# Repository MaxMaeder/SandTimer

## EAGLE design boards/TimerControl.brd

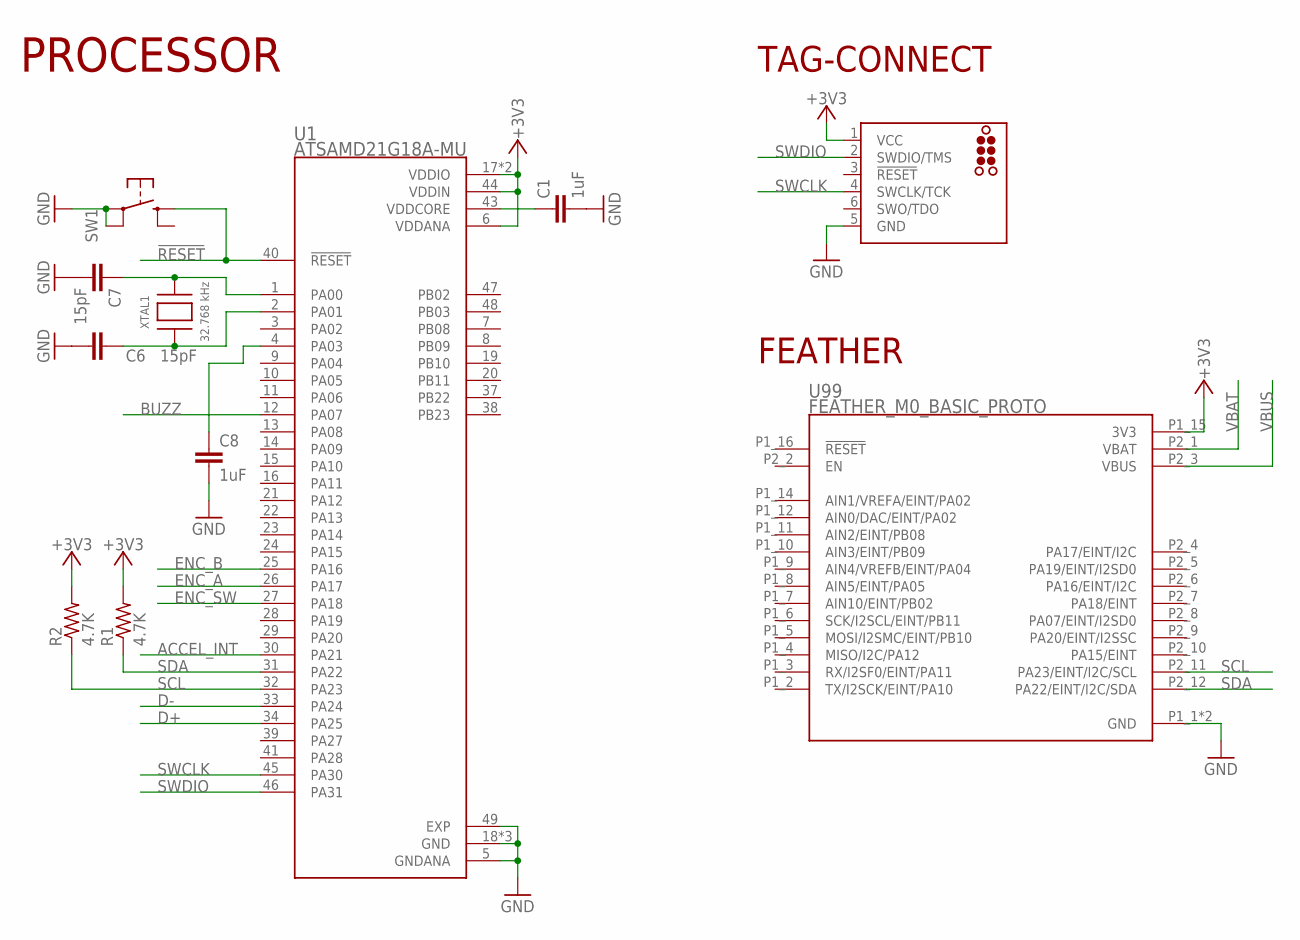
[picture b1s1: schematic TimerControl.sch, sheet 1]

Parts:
C1, C8: 1uF; C0603
C6, C7: 15pF; C0603
J3: TC2030_SWD-MCP-NL; TC2030-MCP-NL
R1, R2: 4.7K; R0603
SW1: KMR2; 2.80X4.60
U1: ATSAMD21G18A-MU; QFN50P700X700X90-49N
U99: FEATHER_M0_BASIC_PROTO; MODULE_FEATHER_M0_BASIC_PROTO
XTAL1: 32.768 kHz; XTAL3215

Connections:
!RESET: SW1.B (S), U1.40 (!RESET)
+3V3: J3.1 (VCC), R1.2, R2.2, U1.6 (VDDANA), U1.17 (VDDIO), U1.36 (VDDIO), U1.44 (VDDIN), U99.P1_15 (3V3); also elsewhere on the board
ACCEL_INT: U1.30 (PA21); also elsewhere on the board
BUZZ: U1.12 (PA07); also elsewhere on the board
D+: U1.34 (PA25); also elsewhere on the board
D-: U1.33 (PA24); also elsewhere on the board
ENC_A: U1.26 (PA17); also elsewhere on the board
ENC_B: U1.25 (PA16); also elsewhere on the board
ENC_SW: U1.27 (PA18); also elsewhere on the board
GND: C1.2, C6.2, C7.2, C8.2, J3.5 (GND), SW1.A, SW1.A' (P1), U1.5 (GNDANA), U1.18 (GND), U1.35 (GND), U1.42 (GND), U1.49 (EXP), U99.P1_1 (GND), U99.P1_13 (GND); also elsewhere on the board
unnamed: C1.1, U1.43 (VDDCORE)
unnamed: C8.1, U1.4 (PA03)
unnamed: C6.1, U1.2 (PA01), XTAL1.P$1
unnamed: C7.1, U1.1 (PA00), XTAL1.P$2
SCL: R2.1, U1.32 (PA23), U99.P2_11 (PA23/EINT/I2C/SCL); also elsewhere on the board
SDA: R1.1, U1.31 (PA22), U99.P2_12 (PA22/EINT/I2C/SDA); also elsewhere on the board
SWCLK: J3.4 (SWCLK/TCK), U1.45 (PA30)
SWDIO: J3.2 (SWDIO/TMS), U1.46 (PA31)
VBAT: U99.P2_1 (VBAT); also elsewhere on the board
VBUS: U99.P2_3 (VBUS); also elsewhere on the board

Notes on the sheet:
TAG-CONNECT
PROCESSOR
FEATHER

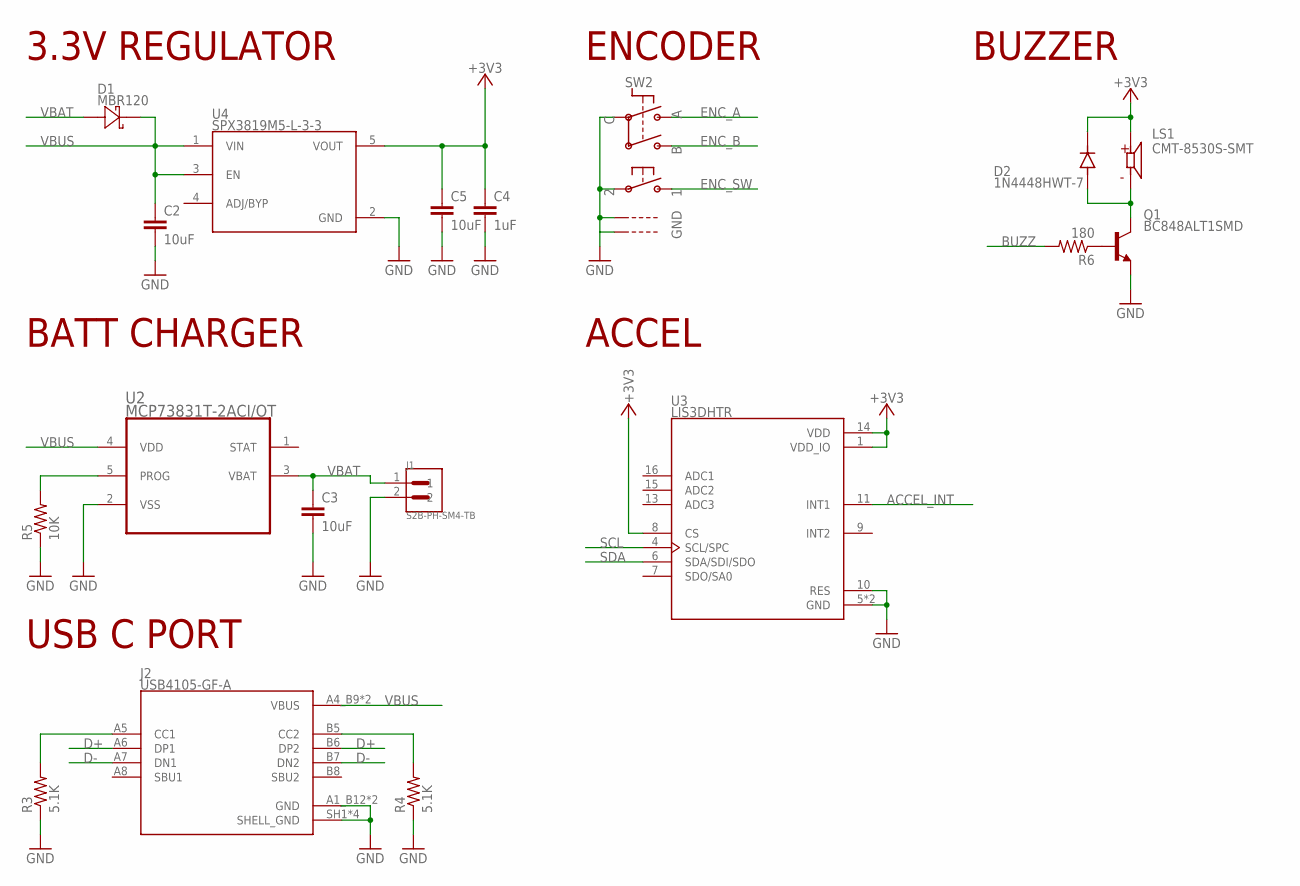
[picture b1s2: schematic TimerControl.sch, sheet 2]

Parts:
C2, C3, C5: 10uF; C0603
C4: 1uF; C0603
D1: MBR120; SOD−123FL
D2: 1N4448HWT-7; SODFL1608X65N
J1: S2B-PH-SM4-TB; JST_S2B-PH-SM4-TB
J2: USB4105-GF-A; GCT_USB4105-GF-A
LS1: CMT-8530S-SMT; CUI_CMT-8530S-SMT
Q1: BC848ALT1SMD; SOT23
R3, R4: 5.1K; R0603
R5: 10K; R0603
R6: 180; R0603
SW2: PEC11R_BOURNS_PEC11; PEC11R
U2: MCP73831T-2ACI/OT; SOT95P280X145-5N
U3: LIS3DHTR; XDCR_LIS3DHTR
U4: SPX3819M5-L-3-3; SOT95P280X145-5N

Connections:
+3V3: C4.1, C5.1, D2.C (K), LS1.P, U3.1 (VDD_IO), U3.8 (CS), U3.14 (VDD), U4.5 (VOUT); also elsewhere on the board
ACCEL_INT: U3.11 (INT1); also elsewhere on the board
BUZZ: R6.2; also elsewhere on the board
D+: J2.A6 (DP1), J2.B6 (DP2); also elsewhere on the board
D-: J2.A7 (DN1), J2.B7 (DN2); also elsewhere on the board
ENC_A: SW2.P$A; also elsewhere on the board
ENC_B: SW2.P$B; also elsewhere on the board
ENC_SW: SW2.P$1; also elsewhere on the board
GND: C2.2, C3.2, C4.2, C5.2, J1.2, J2.A1_B12 (GND), J2.B1_A12 (GND), J2.SH1 (SHELL_GND), J2.SH2 (SHELL_GND), J2.SH3 (SHELL_GND), J2.SH4 (SHELL_GND), Q1.2 (E), R3.1, R4.1, R5.1, SW2.P$2, SW2.P$C, SW2.P$GND1, SW2.P$GND2, U2.2 (VSS), U3.5 (GND), U3.10 (RES), U3.12 (GND), U4.2 (GND); also elsewhere on the board
unnamed: R5.2, U2.5 (PROG)
unnamed: J2.B5 (CC2), R4.2
unnamed: D2.A, LS1.N, Q1.3 (C)
unnamed: Q1.1 (B), R6.1
unnamed: J2.A5 (CC1), R3.2
SCL: U3.4 (SCL/SPC); also elsewhere on the board
SDA: U3.6 (SDA/SDI/SDO); also elsewhere on the board
VBAT: C3.1, D1.A (2), J1.1, U2.3 (VBAT); also elsewhere on the board
VBUS: C2.1, D1.C (1), J2.A4_B9 (VBUS), J2.B4_A9 (VBUS), U2.4 (VDD), U4.1 (VIN), U4.3 (EN); also elsewhere on the board

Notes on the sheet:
3.3V REGULATOR
BATT CHARGER
USB C PORT
ENCODER
ACCEL
BUZZER

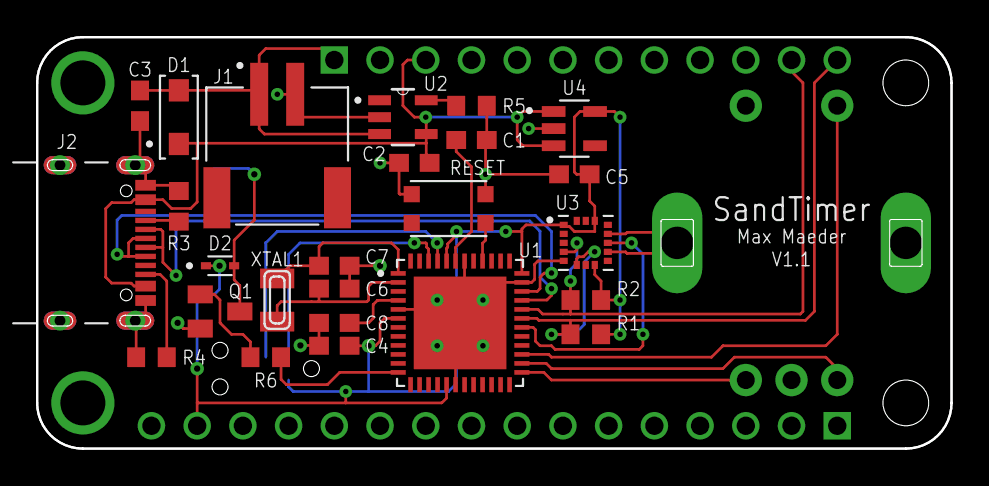
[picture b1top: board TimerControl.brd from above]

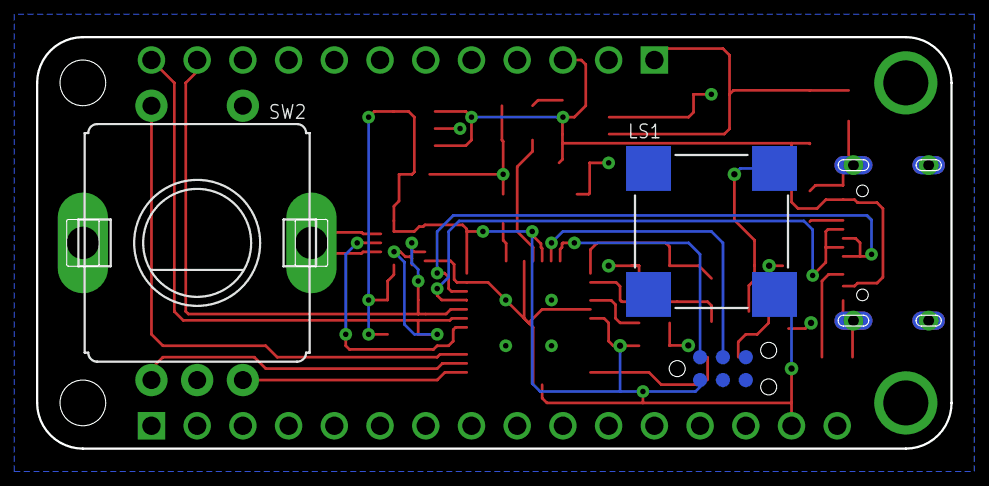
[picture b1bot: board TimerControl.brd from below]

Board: 2 copper layers, 50.8 x 22.9 mm, 29 parts (3 on the bottom side), 25 nets.

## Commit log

2024-01-23 Init
2024-05-12 Reorg

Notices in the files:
parts and their libraries:
Tag-Connect: ©2009 ROFA.cz - modified and updated by Robert Darlington ‹rdarlington@gmail.com›
